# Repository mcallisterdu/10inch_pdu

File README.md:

# 10-Inch 1U Rack Low-Voltage DC PDU

A parametric **10-inch 1U rack-mount low-voltage DC Power Distribution Unit (PDU)** cage and faceplate designed in [`build123d`](https://github.com/gumyr/build123d) for support-free flat-bed 3D printing on a **Bambu Lab X1C**.

## Overview & Dimensions

- **Form Factor:** 10" 1U standard (`254.0 mm` W × `140.0 mm` D × `44.45 mm` H)
- **Rack Mounting:** 4× horizontal M6 stadium slots (`236.5 mm` × `31.75 mm` pitch)
- **Internal Mounting:** M3 heat-set threaded inserts (`4.2 mm` bores) + press-fit retaining cradle

## Supported Internal Hardware

1. **AC Inlet (Front-Left):** IEC C14 with fuse & switch (10A 250V, `47.2 × 27.5 mm` cutout, 2× M3 inserts)
2. **12V-to-5V Buck Converter (Middle-Left):** TOBSUN EA50-5V
3. **Smart Energy Meter (Front-Center):** Shelly EM Mini Gen4 (1-Ch 16A) in a recessed press-fit cradle
4. **12V Power Supply (Front/Middle-Right):** NOVBO ECV-036P-012-31 (36W non-dimmable)
5. **5V+ & 12V+ Distribution (Rear-Left / Rear-Right):** 2× 4-position red terminal bus bars
6. **Shared Ground Rail (Center-Rear, Staggered):** 1× 8-position green terminal bus bar

## 3D Printing (Bambu Lab X1C)

Use **`pdu_10inch_1u_x1c.3mf`** to open the ready-to-print project in **Bambu Studio** with the applied slicing settings pre-configured:

- **Printer:** Bambu Lab X1C
- **Build Plate:** Textured PEI Plate
- **Nozzle:** 0.4 mm Hardened Steel
- **Material:** PETG
- **Orientation:** Flat on bed (support-free)

## Repository Files

| File | Description |
| :--- | :--- |
| `pdu_10inch_1u.py` | Parametric `build123d` CAD source script |
| `pdu_10inch_1u_x1c.3mf` | Bambu Studio project file with X1C slicing settings (Textured PEI, 0.4mm hardened nozzle, PETG) |
| `pdu_10inch_1u.3mf` / `.step` / `.stl` | Raw exported 3D CAD / mesh geometry |
| `bambu_x1c_petg_project_settings.json` | Exported Bambu Studio PETG project settings reference |
| `pdu_preview_iso.svg` | Isometric vector preview |
| [`WIRING.md`](WIRING.md) | AC/DC wiring schematic, wire gauges, inline fuse placements, and device connector guide |
| [`pcb/PCB_DESIGN.md`](pcb/PCB_DESIGN.md) | Prototype integrated power PCB (Mean Well IRM-60-12, TI LMR33640 12V→5V 4A buck, fused 12V/5V/GND rails, BOM, KiCad files, 3D STEP & Gerbers) |

## Regenerating CAD Exports

```zsh
.venv/bin/python pdu_10inch_1u.py
```

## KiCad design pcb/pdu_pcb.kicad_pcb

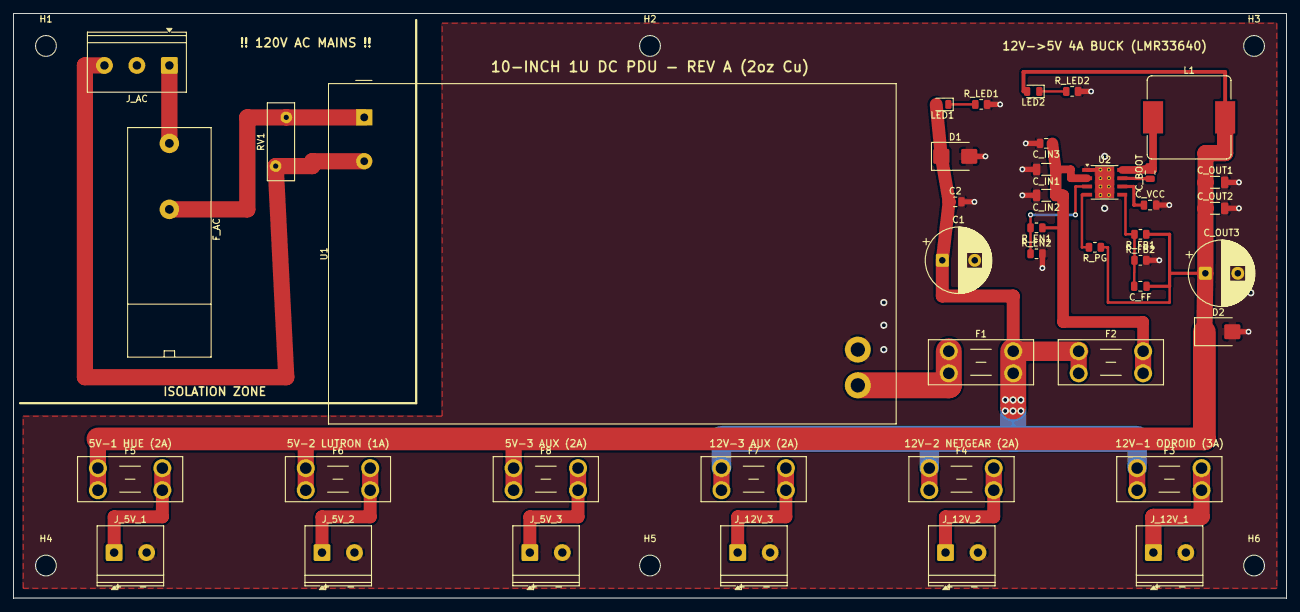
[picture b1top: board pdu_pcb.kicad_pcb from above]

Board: 2 copper layers, 196.0 x 90.0 mm, 48 parts (0 on the bottom side), 22 nets.

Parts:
C1: 470uF_25V; CP_Radial_D10.0mm_P5.00mm
C2: 100nF_25V; C_0805_2012Metric
C_BOOT: 100nF_25V; C_0805_2012Metric
C_FF: 22pF; C_0805_2012Metric
C_IN1: 22uF_25V; C_1206_3216Metric
C_IN2: 10uF_25V; C_1206_3216Metric
C_IN3: 100nF_25V; C_0805_2012Metric
C_OUT1, C_OUT2: 47uF_10V; C_1206_3216Metric
C_OUT3: 470uF_16V; CP_Radial_D10.0mm_P5.00mm
C_VCC: 1uF_16V; C_0805_2012Metric
D1: SMBJ15A; D_SMB
D2: SMBJ5.8A; D_SMB
F1: 4A_MINI; Fuseholder_Blade_Mini_Keystone_3568
F2, F4, F5, F7, F8: 2A_MINI; Fuseholder_Blade_Mini_Keystone_3568
F3: 3A_MINI; Fuseholder_Blade_Mini_Keystone_3568
F6: 1A_MINI; Fuseholder_Blade_Mini_Keystone_3568
F_AC: 2A_T_250V; Fuseholder_Cylinder-5x20mm_Bulgin_FX0457_Horizontal_Closed
H1, H2, H3, H4, H5, H6: M3; MountingHole_3.2mm_M3
J_5V_1: 5V_HUE; TerminalBlock_Phoenix_PT-1,5-2-5.0-H_1x02_P5.00mm_Horizontal
J_5V_2: 5V_LUTRON; TerminalBlock_Phoenix_PT-1,5-2-5.0-H_1x02_P5.00mm_Horizontal
J_5V_3: 5V_AUX; TerminalBlock_Phoenix_PT-1,5-2-5.0-H_1x02_P5.00mm_Horizontal
J_12V_1: 12V_ODROID; TerminalBlock_Phoenix_PT-1,5-2-5.0-H_1x02_P5.00mm_Horizontal
J_12V_2: 12V_NETGEAR; TerminalBlock_Phoenix_PT-1,5-2-5.0-H_1x02_P5.00mm_Horizontal
J_12V_3: 12V_AUX; TerminalBlock_Phoenix_PT-1,5-2-5.0-H_1x02_P5.00mm_Horizontal
J_AC: AC_120V_IN; TerminalBlock_Phoenix_PT-1,5-3-5.0-H_1x03_P5.00mm_Horizontal
L1: 10uH_8.5A; L_Bourns_SRP1245A
LED1: 12V_OK_GRN; LED_0805_2012Metric
LED2: 5V_OK_GRN; LED_0805_2012Metric
RV1: S14K150_MOV; RV_Disc_D12mm_W4.2mm_P7.5mm
R_EN1: 100k; R_0805_2012Metric
R_EN2: 15k; R_0805_2012Metric
R_FB1: 100k_1%; R_0805_2012Metric
R_FB2: 24.9k_1%; R_0805_2012Metric
R_LED1: 2.2k; R_0805_2012Metric
R_LED2: 1.0k; R_0805_2012Metric
R_PG: 100k; R_0805_2012Metric
U1: IRM-60-12; Converter_ACDC_MeanWell_IRM-60-xx_THT
U2: LMR33640ADDA; Texas_HSOP-8-1EP_3.9x4.9mm_P1.27mm_ThermalVias

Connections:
+5V_BUS: C_FF.1, C_OUT1.1, C_OUT2.1, C_OUT3.1, D2.1, F5.1, F6.1, F8.1, L1.2, LED2.2, R_FB1.1, R_PG.1
+5V_CH1_HUE: F5.2, J_5V_1.1
+5V_CH2_LUTRON: F6.2, J_5V_2.1
+5V_CH3_AUX: F8.2, J_5V_3.1
+12V_BUCK_IN: C_IN1.1, C_IN2.1, C_IN3.1, F2.2, R_EN1.1, U2.2
+12V_BUS: C1.1, C2.1, D1.1, F1.2, F2.1, F3.1, F4.1, F7.1, LED1.2
+12V_CH1_ODROID: F3.2, J_12V_1.1
+12V_CH2_NETGEAR: F4.2, J_12V_2.1
+12V_CH3_AUX: F7.2, J_12V_3.1
+12V_RAW: F1.1, U1.3
AC_L: F_AC.1, J_AC.1
AC_L_FUSED: F_AC.2, RV1.1, U1.1
AC_N: J_AC.3, RV1.2, U1.2
BUCK_BOOT: C_BOOT.1, U2.7
BUCK_EN: R_EN1.2, R_EN2.1, U2.3
BUCK_FB: C_FF.2, R_FB1.2, R_FB2.1, U2.5
BUCK_PG: R_PG.2, U2.4
BUCK_SW: C_BOOT.2, L1.1, U2.8
BUCK_VCC: C_VCC.1, U2.6
GND: C1.2, C2.2, C_IN1.2, C_IN2.2, C_IN3.2, C_OUT1.2, C_OUT2.2, C_OUT3.2, C_VCC.2, D1.2, D2.2, J_5V_1.2, J_5V_2.2, J_5V_3.2, J_12V_1.2, J_12V_2.2, J_12V_3.2, R_EN2.2, R_FB2.2, R_LED1.2, R_LED2.2, U1.4, U2.1, U2.9
LED5_K: LED2.1, R_LED2.1
LED12_K: LED1.1, R_LED1.1

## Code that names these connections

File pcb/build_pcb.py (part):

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        "H6": (191.0, 85.0, 0),

        # AC Mains Primary Zone (Left-Front, strictly isolated)
        "J_AC": (24.0, 8.0, 180),       # Pin1=AC_L at (24,8), Pin2=NC at (19,8), Pin3=AC_N at (14,8)
        "F_AC": (24.0, 20.0, 270),      # Pin1=AC_L at (24,20), Pin2=AC_L_FUSED at (24,30.16)
        "RV1":  (42.0, 16.0, 270),      # Pin1=AC_L_FUSED at (42,16), Pin2=AC_N at (42,23.5)

        # Mean Well IRM-60-12 (87.5 x 53.0 mm: X=[48.45, 135.95], Y=[10.30, 63.25])
        "U1":   (54.0, 16.0, 0),
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        pad_pos(fps["U1"], "1"),
    ], width_mm=2.5, layer=pcbnew.F_Cu)

    # Route AC_N cleanly along the left side (X=11) below F_AC (Y=55) up to RV1 & U1 Pin 2
    add_poly_tracks(board, n_ac_n, [
        pad_pos(fps["J_AC"], "3"),
        (11.0, 8.0),
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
